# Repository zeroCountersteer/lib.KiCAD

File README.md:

# lib.KiCAD

`lib.KiCAD` is a personal KiCad 10+ content library distributed both as a normal git checkout and as a static KiCad Plugin and Content Manager (PCM) v2 repository. It contains the existing grouped `lib` library plus audited Allwinner A33 and X-Powers AXP223 symbols and footprints.

## Source layout

* `symbols/` — grouped `lib.kicad_sym`, `SoC_Allwinner.kicad_sym`, and `PMIC_XPowers.kicad_sym`.
* `footprints/` — `lib.pretty`, `Package_SoC.pretty`, and `Package_PMIC.pretty`.
* `3dmodels/` — the existing custom `lib.3dshapes` collection.
* `pcm/` — v2 package metadata template.
* `scripts/` — importer, portability normalizer, validator, package builder, and repository-index generator.

## Direct git use

Add `symbols/*.kicad_sym` in Symbol Editor → Manage Symbol Libraries and add the three `footprints/*.pretty` directories in Footprint Libraries. Do not override `KICAD10_3RD_PARTY`: custom references use the canonical PCM installation path `${KICAD10_3RD_PARTY}/3dmodels/com_github_zerocountersteer_lib-kicad/lib.3dshapes/...`, while stock `${KICAD10_3DMODEL_DIR}` references are unchanged. On a machine where the PCM package has not been installed, add that model directory under the same package-id path in KiCad's normal third-party directory. The PCM build removes references to legacy external model libraries that are not shipped by this package, so a clean PCM installation never points at an unavailable KiCad 6 or third-party model tree.

## Validate and build locally

```sh
python3 scripts/validate_library.py
mkdir -p dist
python3 scripts/build_pcm_package.py --version 0.1.0 \
  --output dist/lib.KiCAD-0.1.0.zip
unzip -l dist/lib.KiCAD-0.1.0.zip
```

The archive contains `symbols/`, `footprints/`, `3dmodels/`, `templates/`, and `metadata.json`. It is deterministic and emits a `.sha256` sidecar. Run `python3 scripts/validate_pcm_package.py dist/lib.KiCAD-0.1.0.zip` to verify the archive layout and all packaged 3D model references.

## Releases and PCM repository

Create an immutable semantic-version release:

```sh
git tag v0.1.0
git push origin v0.1.0
```

The tag workflow validates the library, builds `lib.KiCAD-0.1.0.zip`, creates the GitHub Release asset, derives prior tagged releases from the GitHub API, generates `repository.json` and `packages.json`, and deploys those files to GitHub Pages. The expected repository URL is:

`https://zerocountersteer.github.io/lib.KiCAD/repository.json`

In KiCad 10, open Preferences → Manage Plugin and Content Manager → Manage Repositories, add that URL, and refresh. The update flow is: push to `main` → GitHub rebuilds the moving `rolling` release → Pages index updates → KiCad sees the new development version. Stable immutable releases still use the tag flow above. The rolling package is versioned as `0.99.<GitHub run number>` so every push is a real PCM update and sorts above the current `0.x` stable releases. The ZIP is always uploaded as the single mutable `lib.KiCAD-rolling.zip` asset in the `rolling` release, so the release does not accumulate one asset per update.

Enable Settings → Pages once in the GitHub repository, choose **GitHub Actions** as the source, and keep the `github-pages` environment available. No package ZIP is copied to Pages; it remains a GitHub Release asset, while the rolling asset is intentionally replaced on each successful `main` build.

## Component audits and provenance

The A33 conversion contains all 282 sparse TFBGA balls on the MiniDev 17×17 grid, with the confirmed correction `PG8=B16` and `PG9=A16`. The AXP223 conversion contains pads 1–69, names pad 69 `EP/GND`, and uses three smaller F.Paste apertures rather than one solid exposed-pad aperture. Thermal vias are left to the board designer.

Both components are derived from the MIT-licensed A33-MiniDev project; see `THIRD_PARTY_NOTICES.md`. No MiniDev 3D model is shipped because redistributable provenance was not independently established. Existing CAD content has mixed provenance and is not falsely declared uniformly MIT; see `LICENSE`.

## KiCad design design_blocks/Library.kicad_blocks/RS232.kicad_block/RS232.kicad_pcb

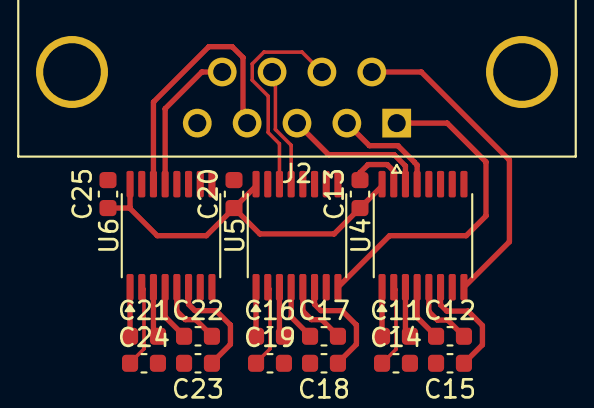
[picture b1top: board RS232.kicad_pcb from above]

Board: 4 copper layers, 19 parts (0 on the bottom side), 28 nets.

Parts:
C11, C12, C13, C14, C15, C16, C17, C18, C19, C20, C21, C22, C23, C24, C25: 0.1мкФ; C_0603_1608Metric
J2: DE9_Pins_MountingHoles; DSUB-9_Pins_Horizontal_P2.77x2.84mm_EdgePinOffset4.94mm_Hou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
U4, U5, U6: MAX3232CPWR; TSSOP-16_4.4x5mm_P0.65mm

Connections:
/RS232/CTS: J2.8, U5.13 (R1IN)
/RS232/DCD: J2.1, U5.8 (R2IN)
/RS232/DSR: J2.6, U4.8 (R2IN)
/RS232/DTR: J2.4, U6.14 (T1OUT)
/RS232/RI: J2.9, U6.13 (R1IN)
/RS232/RTS: J2.7, U5.14 (T1OUT)
/RS232/RXD: J2.2, U4.13 (R1IN)
/RS232/TXD: J2.3, U4.14 (T1OUT)
/RS232/VCC: C13.1, C20.1, C25.1, U4.16 (VCC), U5.16 (VCC), U6.16 (VCC)
GND: C13.2, C14.2, C15.2, C18.2, C19.2, C20.2, C23.2, C24.2, C25.2, J2.5, J2.SH (PAD), U4.15 (GND), U5.15 (GND), U6.15 (GND)
unnamed: C11.1, U4.1 (C1+)
unnamed: C11.2, U4.3 (C1-)
unnamed: C12.1, U4.4 (C2+)
unnamed: C12.2, U4.5 (C2-)
unnamed: C14.1, U4.2 (VS+)
unnamed: C15.1, U4.6 (VS-)
unnamed: C16.1, U5.1 (C1+)
unnamed: C16.2, U5.3 (C1-)
unnamed: C17.1, U5.4 (C2+)
unnamed: C17.2, U5.5 (C2-)
unnamed: C19.1, U5.2 (VS+)
unnamed: C18.1, U5.6 (VS-)
unnamed: C21.1, U6.1 (C1+)
unnamed: C21.2, U6.3 (C1-)
unnamed: C22.1, U6.4 (C2+)
unnamed: C22.2, U6.5 (C2-)
unnamed: C24.1, U6.2 (VS+)
unnamed: C23.1, U6.6 (VS-)

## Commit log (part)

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2026-03-18 BQ77915
